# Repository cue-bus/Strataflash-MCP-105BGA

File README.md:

# Strataflash-MCP-105BGA
Breakout adapters for Intel/Numonyx Strataflash MCP chips in 105BGA package

These adapters can be used to interface with these BGA chips using standard chip programmers such as the XGecu T56. The breakouts feature a NOR section and NAND section if the chip has it. The chips' NOR sections have been successfully read using a T56 programmer using the Micron MT28GUxxxAAA2EGC algorithm, where xxx is the size of the die to be read. Note that the T56 will complain both about unconnected pins as well as the incorrect chip ID. To get the T56 to read them, you can uncheck the "Pin Check" and "Check ID" options and the read will still be successful. 
For the NOR section, make sure to use the 8 pin cable that connects the ISP header to the 8 extra pins in the NOR section. Make sure to respect pin 1 orientation on both ends.

Since these chips have up to 4 different dies, you can cycle through each CE line one by one. Select the CE jumper for the die you want to read (CE1 and 2 for NOR, CE3 and 4 for NAND) by soldering the center pad to the left pad. Solder the other CE center pads to the right, which connects them to VCC and holds them unasserted. Make sure you do not have more than 1 CE center pad jumpered to the left.

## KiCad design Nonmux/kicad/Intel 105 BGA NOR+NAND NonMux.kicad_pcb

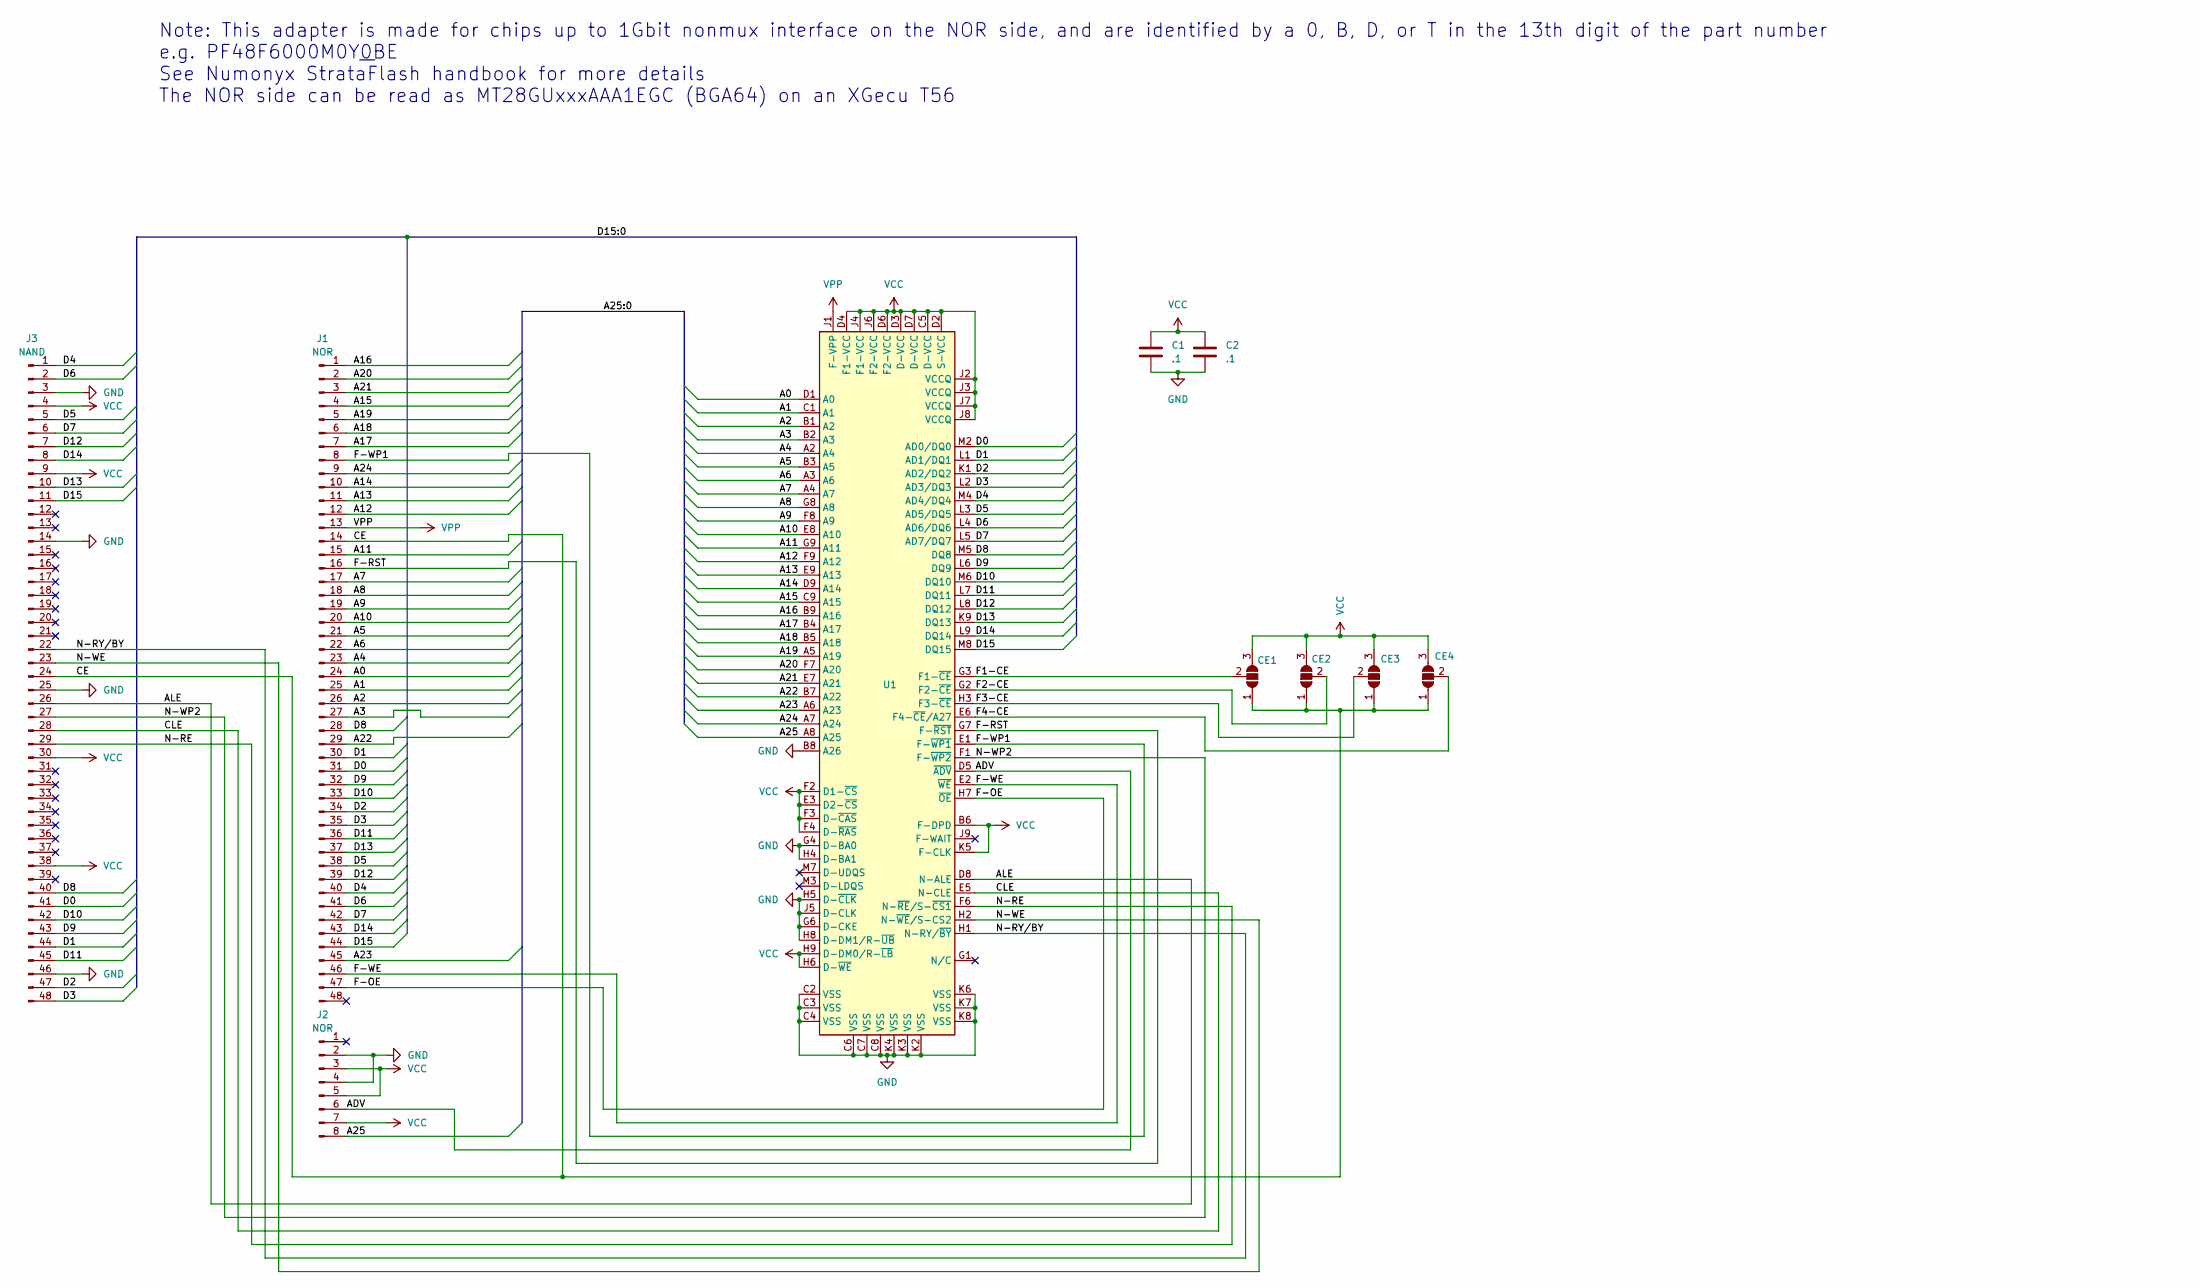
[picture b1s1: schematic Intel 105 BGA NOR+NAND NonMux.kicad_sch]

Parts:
C1, C2: .1; C_0805_2012Metric_Pad1.18x1.45mm_HandSolder
CE1, CE2, CE3, CE4: SolderJumper_2_Open; SolderJumper-3_P1.3mm_Open_RoundedPad1.0x1.5mm
J1: NOR; DIP-48_W15.24mm_Socket_LongPads
J2: NOR; PinHeader_1x08_P2.54mm_Vertical
J3: NAND; DIP-48_W15.24mm_Socket_LongPads
U1: Intel BGA105 x16D 9x11

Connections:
/A0: J1.24, U1.D1 (A0)
/A1: J1.25, U1.C1 (A1)
/A2: J1.26, U1.B1 (A2)
/A3: J1.27, U1.B2 (A3)
/A4: J1.23, U1.A2 (A4)
/A5: J1.21, U1.B3 (A5)
/A6: J1.22, U1.A3 (A6)
/A7: J1.17, U1.A4 (A7)
/A8: J1.18, U1.G8 (A8)
/A9: J1.19, U1.F8 (A9)
/A10: J1.20, U1.E8 (A10)
/A11: J1.15, U1.G9 (A11)
/A12: J1.12, U1.F9 (A12)
/A13: J1.11, U1.E9 (A13)
/A14: J1.10, U1.D9 (A14)
/A15: J1.4, U1.C9 (A15)
/A16: J1.1, U1.B9 (A16)
/A17: J1.7, U1.B4 (A17)
/A18: J1.6, U1.B5 (A18)
/A19: J1.5, U1.A5 (A19)
/A20: J1.2, U1.F7 (A20)
/A21: J1.3, U1.E7 (A21)
/A22: J1.29, U1.B7 (A22)
/A23: J1.45, U1.A6 (A23)
/A24: J1.9, U1.A7 (A24)
/A25: J2.8, U1.A8 (A25)
/ADV: J2.6, U1.D5 (~ADV)
/ALE: J3.26, U1.D8 (N-ALE)
/CE: CE1.1 (A), CE2.1 (A), CE3.1 (A), CE4.1 (A), J1.14, J3.24
/CLE: J3.28, U1.E5 (N-CLE)
/D0: J1.31, J3.41, U1.M2 (AD0/DQ0)
/D1: J1.30, J3.44, U1.L1 (AD1/DQ1)
/D2: J1.34, J3.47, U1.K1 (AD2/DQ2)
/D3: J1.35, J3.48, U1.L2 (AD3/DQ3)
/D4: J1.40, J3.1, U1.M4 (AD4/DQ4)
/D5: J1.38, J3.5, U1.L3 (AD5/DQ5)
/D6: J1.41, J3.2, U1.L4 (AD6/DQ6)
/D7: J1.42, J3.6, U1.L5 (AD7/DQ7)
/D8: J1.28, J3.40, U1.M5 (DQ8)
/D9: J1.32, J3.43, U1.L6 (DQ9)
/D10: J1.33, J3.42, U1.M6 (DQ10)
/D11: J1.36, J3.45, U1.L7 (DQ11)
/D12: J1.39, J3.7, U1.L8 (DQ12)
/D13: J1.37, J3.10, U1.K9 (DQ13)
/D14: J1.43, J3.8, U1.L9 (DQ14)
/D15: J1.44, J3.11, U1.M8 (DQ15)
/F1-CE: CE1.2 (C), U1.G3 (F1-~CE)
/F2-CE: CE2.2 (C), U1.G2 (F2-~CE)
/F3-CE: CE3.2 (C), U1.H3 (F3-~CE)
/F4-CE: CE4.2 (C), U1.E6 (F4-~CE/A27)
/F-OE: J1.47, U1.H7 (~OE)
/F-RST: J1.16, U1.G7 (F-~RST)
/F-WE: J1.46, U1.E2 (~WE)
/F-WP1: J1.8, U1.E1 (F-~WP1)
/N-RE: J3.29, U1.F6 (N-~RE/S-~CS1)
/N-RY/BY: J3.22, U1.H1 (N-RY/~BY)
/N-WE: J3.23, U1.H2 (N-~WE/S-CS2)
/N-WP2: J3.27, U1.F1 (F-~WP2)
GND: C1.2, C2.2, J2.2, J2.4, J3.3, J3.14, J3.25, J3.46, U1.B8 (A26), U1.C2 (VSS), U1.C3 (VSS), U1.C4 (VSS), U1.C6 (VSS), U1.C7 (VSS), U1.C8 (VSS), U1.G4 (D-BA0), U1.G6 (D-CKE), U1.H4 (D-BA1), U1.H5 (D-~CLK), U1.H8 (D-DM1/R-~UB), U1.J5 (D-CLK), U1.K2 (VSS), U1.K3 (VSS), U1.K4 (VSS), U1.K6 (VSS), U1.K7 (VSS), U1.K8 (VSS)
VCC: C1.1, C2.1, CE1.3 (B), CE2.3 (B), CE3.3 (B), CE4.3 (B), J2.3, J2.5, J2.7, J3.4, J3.9, J3.30, J3.38, U1.B6 (F-DPD), U1.C5 (D-VCC), U1.D2 (S-VCC), U1.D3 (D-VCC), U1.D4 (F1-VCC), U1.D6 (F2-VCC), U1.D7 (D-VCC), U1.E3 (D2-~CS), U1.F2 (D1-~CS), U1.F3 (D-~CAS), U1.F4 (D-~RAS), U1.H6 (D-~WE), U1.H9 (D-DM0/R-~LB), U1.J2 (VCCQ), U1.J3 (VCCQ), U1.J4 (F1-VCC), U1.J6 (F2-VCC), U1.J7 (VCCQ), U1.J8 (VCCQ), U1.K5 (F-CLK)
VPP: J1.13, U1.J1 (F-VPP)

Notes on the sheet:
Note: This adapter is made for chips up to 1Gbit nonmux interface on the NOR side, and are identified by a 0, B, D, or T in the 13th digit of the part number e.g. PF48F6000M0Y0BE See Numonyx StrataFlash handbook for more details The NOR side can be read as MT28GUxxxAAA1EGC (BGA64) on an XGecu T56

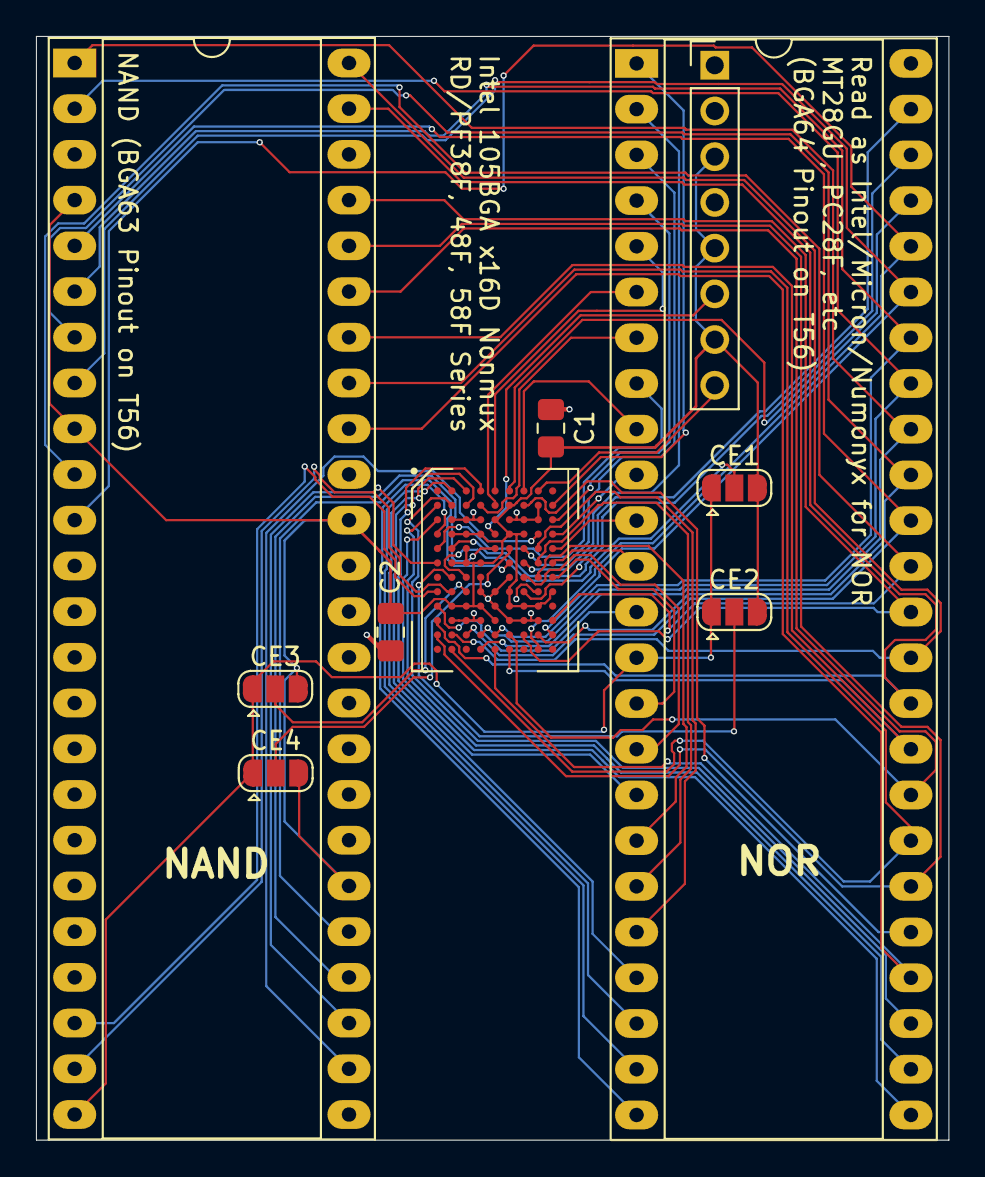
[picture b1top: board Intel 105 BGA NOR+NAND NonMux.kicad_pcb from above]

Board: 2 copper layers, 50.7 x 61.3 mm, 10 parts (0 on the bottom side), 61 nets.

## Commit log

2024-11-10 Create LICENSE
2024-11-10 moved files
2025-02-12 Added nonmux
2025-02-12 Added symbols
